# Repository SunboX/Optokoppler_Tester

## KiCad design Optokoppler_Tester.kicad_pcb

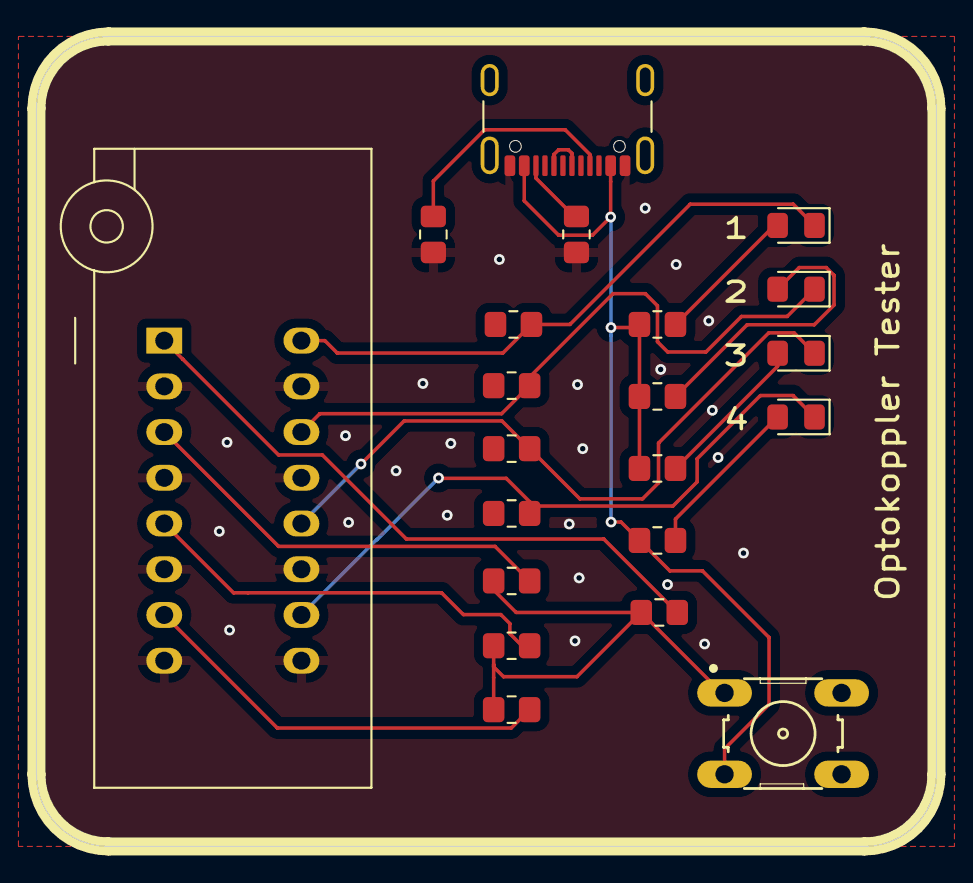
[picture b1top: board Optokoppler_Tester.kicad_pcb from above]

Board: 2 copper layers, 50.0 x 45.0 mm, 21 parts (0 on the bottom side), 18 nets.

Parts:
D1, D2, D3, D4: LED; LED_0805_2012Metric_Pad1.15x1.40mm_HandSolder
J1: USB_C_Receptacle_USB2.0; USB_C_Receptacle_GCT_USB4105-xx-A_16P_TopMnt_Horizontal
R1, R2, R3, R4, R9, R10, R11, R12, R17, R18, R19, R20: 220; R_0805_2012Metric_Pad1.20x1.40mm_HandSolder
R8, R16: 5k1; R_0805_2012Metric_Pad1.20x1.40mm_HandSolder
SW1: SW_Push; SW_B3F-1000
U1: LTV-847M; DIP_Socket-16_W4.3_W5.08_W7.62_W10.16_W10.9_3M_216-3340-00-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

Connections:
+5V: J1.A4 (VBUS), J1.A9 (VBUS), J1.B4 (VBUS), J1.B9 (VBUS), R1.1, R2.1, R3.1, R4.1, SW1.3
/CC1: J1.A5 (CC1), R8.1
/CC2: J1.B5 (CC2), R16.1
/D+: J1.A6 (D+), J1.B6 (D+)
GND: J1.A1 (GND), J1.A12 (GND), J1.B1 (GND), J1.B12 (GND), R8.2, R16.2, U1.2, U1.4, U1.6, U1.8, U1.9, U1.11, U1.13, U1.15
unnamed: D1.2 (A), R1.2
unnamed: D1.1 (K), R9.2, U1.16
unnamed: D2.2 (A), R2.2
unnamed: D2.1 (K), R10.2, U1.14
unnamed: D3.2 (A), R3.2
unnamed: D3.1 (K), R11.2, U1.12
unnamed: D4.2 (A), R4.2
unnamed: D4.1 (K), R12.2, U1.10
unnamed: R17.1, R18.1, R19.1, R20.1, SW1.1
unnamed: R17.2, U1.1
unnamed: R18.2, U1.3
unnamed: R19.2, U1.5
unnamed: R20.2, U1.7

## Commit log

2025-07-15 ༼ つ ◕_◕ ༽つ initial commit
2025-07-20 Added versioning
